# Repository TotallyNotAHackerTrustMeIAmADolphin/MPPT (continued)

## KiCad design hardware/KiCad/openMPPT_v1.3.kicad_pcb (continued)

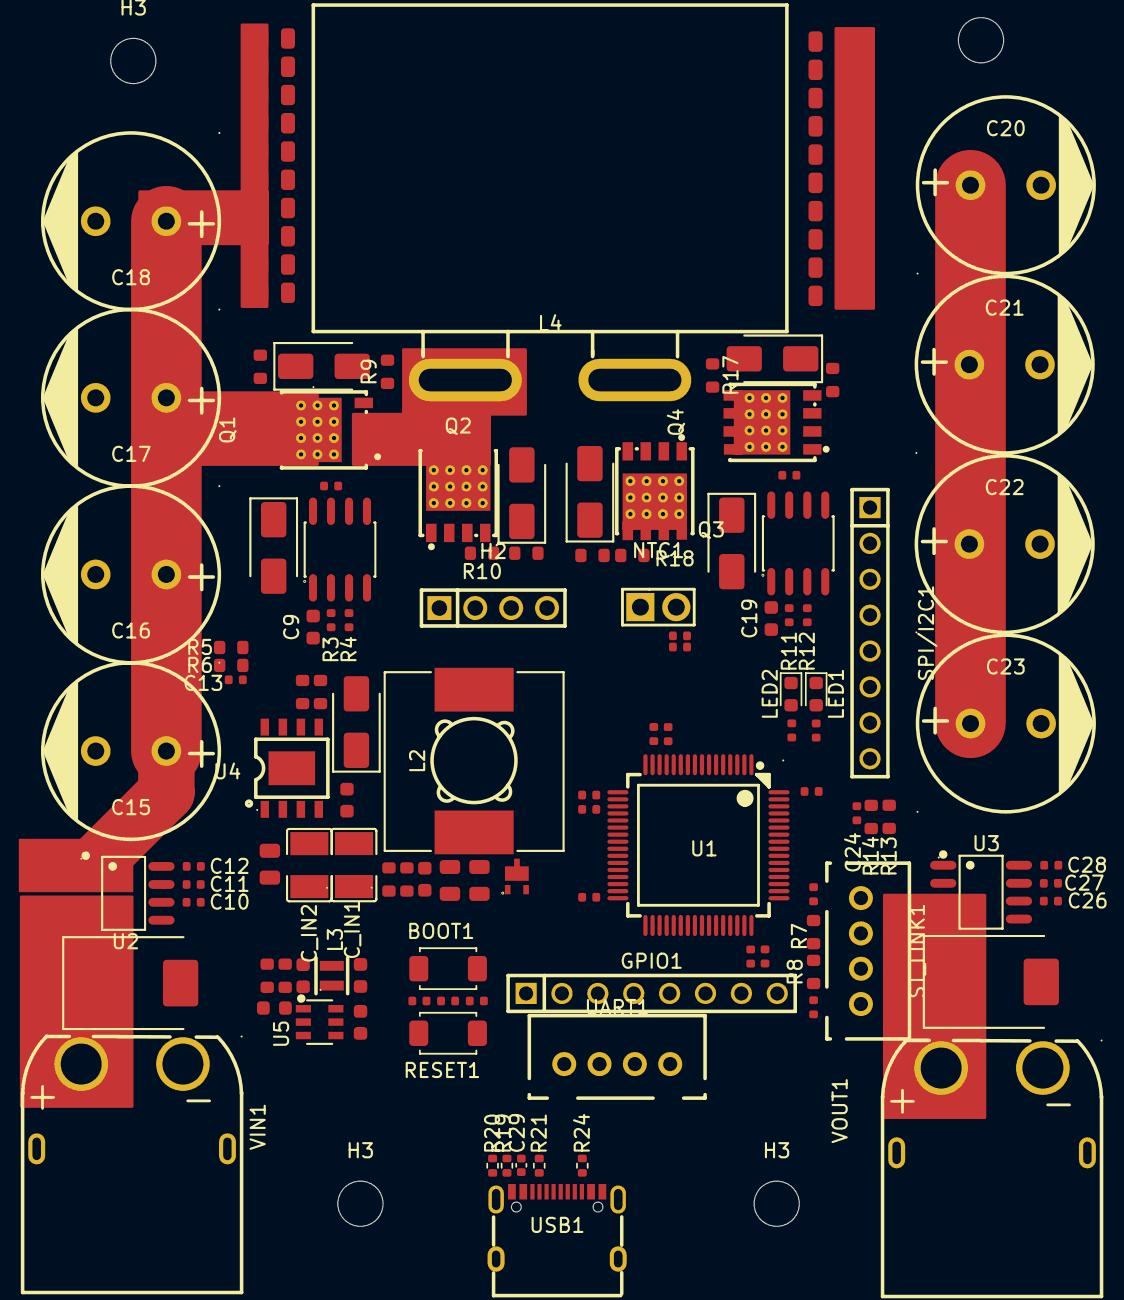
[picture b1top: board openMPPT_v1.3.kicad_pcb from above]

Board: 2 copper layers, 138 parts (0 on the bottom side), 68 nets.

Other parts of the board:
H3#2, H3#3: MountingHole; MountingHole_3.2mm_M3_DIN965

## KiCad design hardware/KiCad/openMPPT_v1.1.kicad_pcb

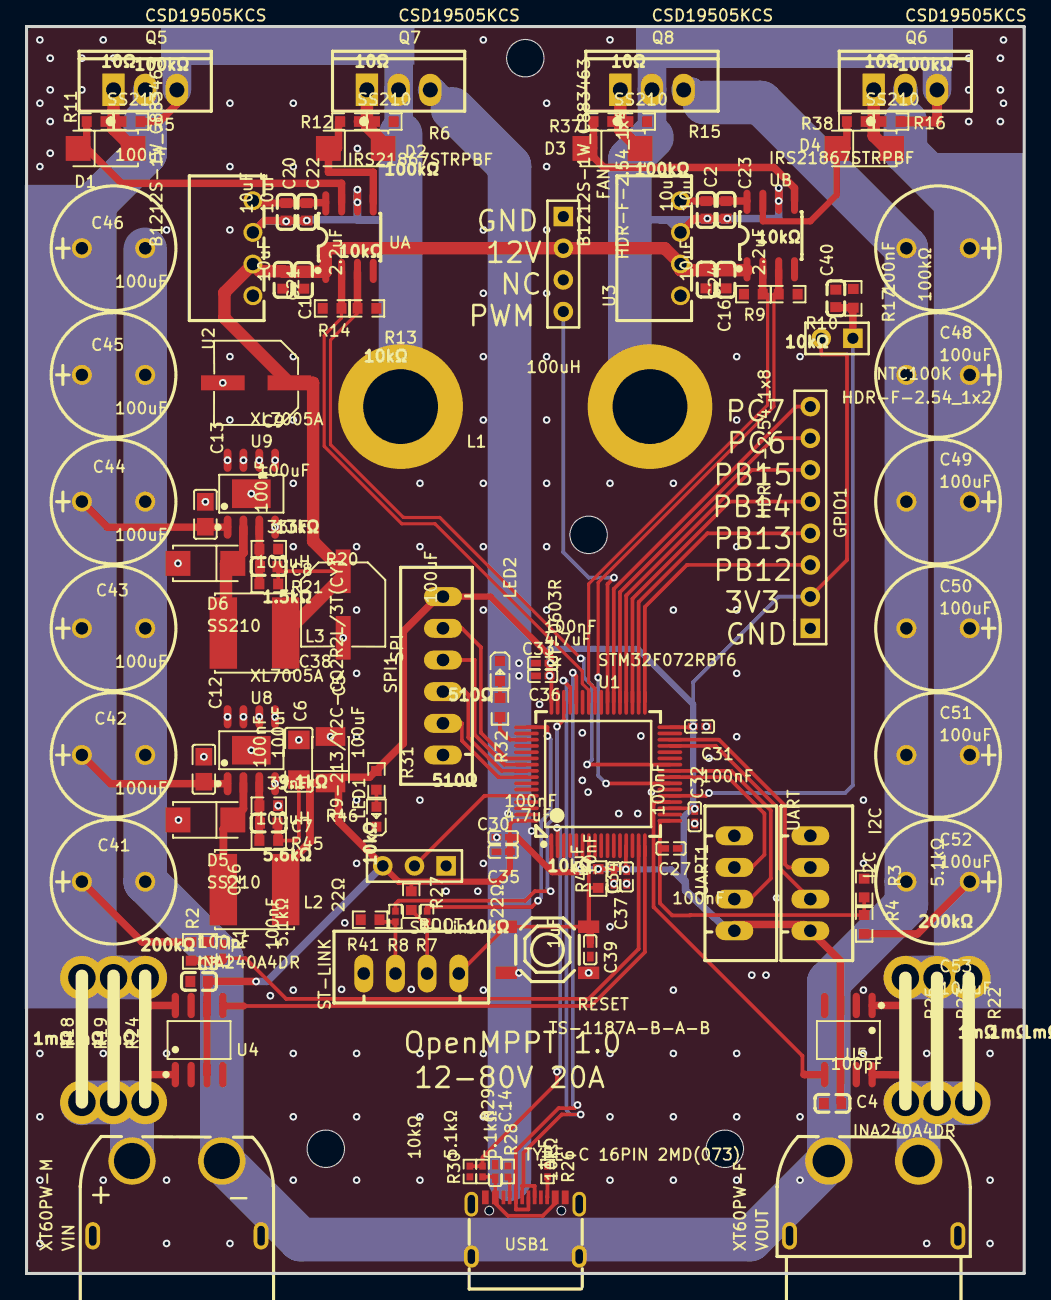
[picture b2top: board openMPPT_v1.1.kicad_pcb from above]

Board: 2 copper layers, 80.0 x 100.0 mm, 121 parts (0 on the bottom side), 62 nets.

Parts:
BOOT1: BOOT; HDR-F-2.54_1X3
C1, C2, C16, C20, C22, C23: 10uF; C0603
C3, C4: 100pF; C0603
C5: 100uF; C1206
C6: 100uF; CASE-B_3528
C7, C8: 33nF; C0603
C9, C38: 100uF; CAP-SMD_BD6.3-L6.6-W6.6-FD
C12, C13: 100nF; C0805
C14, C37, C39: 1uF; C0402
C21, C24: 2.2uF; C0603
C26, C27, C30, C31, C32, C33: 100nF; C0402
C34: 10nF; C0402
C35, C36: 4.7uF; C0402
C40: 100nF; C0603
C41, C42, C43, C44, C45, C46, C48, C49, C50, C51, C52, C53: 100uF; CAP-TH_BD10.0-P5.00-D1.0-FD
D1, D2, D3, D4, D5, D6: SS210; SMA_L4.3-W2.6-LS5.2-RD
FAN: HDR-F-2.54_1x4; HDR-F-2.54_1X4
GPIO1: HDR-F-2.54_1x8; HDR-F-2.54_1X8
Hole_gge64515: Hole_gge64515
Hole_gge4170615605543658: Hole_gge4170615605543658
Hole_gge4170615605543673: Hole_gge4170615605543673
Hole_gge4170615605579758: Hole_gge4170615605579758
I2C: I2C; JST-XH-04-PACKAGE-LONG-PAD
L1: 100uH; INDUCTOR1
L2, L3: 100uH; IND-SMD_L6.0-W6.0
LED1: 19-213/Y2C-CQ2R2L/3T(CY); LED0603-RD-YELLOW
LED2: KT-0603R; LED0603-RD
NTC100K: HDR-F-2.54_1x2; HDR-F-2.54_1X2
Q5, Q6, Q7, Q8: CSD19505KCS; TO-220-3_L10.0-W4.5-P2.54-L
R1, R3: 5.1kΩ; R0603
R2, R4: 200kΩ; R0603
R5, R6, R15, R16, R17: 100kΩ; R0603
R7, R8: 22Ω; R0402
R9, R10, R13, R14, R27, R41, R42: 10kΩ; R0603
R11, R12, R37, R38: 10Ω; R0603
R18, R19, R22, R23, R24, R25: 1mΩ; WIRE-SHUNT
R20: 1.5kΩ; R0603
R21: 13kΩ; R0603
R26, R28: 5.1kΩ; R0402
R29, R30: 10kΩ; R0402
R31, R32: 510Ω; R0603
R45: 9.1kΩ; R0603
R46: 5.6kΩ; R0603
RESET: TS-1187A-B-A-B; SW-SMD_4P-L5.1-W5.1-P3.70-LS6.5-TL-2
SPI1: SPI; JST-XH-06-PACKAGE-LONG-PAD
ST-LINK: ST-Link; JST-XH-04-PACKAGE-LONG-PAD
U1: STM32F072RBT6; LQFP-64_L10.0-W10.0-P0.50-LS12.0-BL
U2, U3: B1212S-1W_C883463; PWRM-TH_B2415S-1W
U4, U5: INA240A4DR; SOIC-8_L4.9-W3.9-P1.27-LS6.0-BL
U8, U9: XL7005A; SOIC-8_L4.9-W3.9-P1.27-LS6.0-BL-EP3.1-1
UA: IRS21867STRPBF; SOIC-8_L5.0-W4.0-P1.27-LS6.0-BL
UART1: UART; JST-XH-04-PACKAGE-LONG-PAD
UB: IRS21867STRPBF; SOIC-8_L5.0-W4.0-P1.27-LS6.0-BL
USB1: TYPE-C 16PIN 2MD(073); USB-C-SMD_TYPE-C-6PIN-2MD-073
VIN: XT60PW-M; CONN-TH_XT60PW-M
VOUT: XT60PW-F; CONN-TH_XT60PW-F

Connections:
3V3: BOOT1.3, C3.2, C4.2, C5.2, C6.1, C7.2, C30.2, C31.2, C32.2, C33.2, C34.2, C35.2, C36.2, C37.2, GPIO1.2, I2C.4, L2.2, NTC100K.2, R27.1, R31.1, R42.2, R45.2, SPI1.6, U1.1, U1.13, U1.19, U1.32, U1.48, U1.64, U4.3, U4.6, U5.3, U5.6, UART1.4
12V: C1.2, C8.2, C9.1, C16.2, C21.1, C24.1, C38.1, FAN.2, L3.2, R21.2, U2.2, U3.2, UA.1, UB.1
BOOT0: BOOT1.2, U1.60
C2_2: C2.2, C23.2, U3.4, UB.8
C8_1: C8.1, R20.2, R21.1, U9.3
CS: SPI1.5, U1.54
D1_1: D1.1, R11.1, UA.7
D2_1: D2.1, R12.1, UA.5
D3_1: D3.1, R37.1, UB.5
D4_1: D4.1, R38.1, UB.7
D6_1: D6.1, L3.1, U9.2
FAN: FAN.4, U1.39
GND: BOOT1.1, C1.1, C3.1, C4.1, C5.1, C6.2, C9.2, C12.1, C13.1, C14.1, C16.1, C21.2, C24.2, C26.1, C27.1, C30.1, C31.1, C32.1, C33.1, C34.1, C35.1, C36.1, C37.1, C38.2, C39.1, C40.1, C41.2, C42.2, C43.2, C44.2, C45.2, C46.2, C48.2, C49.2, C50.2, C51.2, C52.2, C53.2, D5.2, D6.2, FAN.1, GPIO1.1, I2C.1, LED1.1, LED2.1, Q7.3, Q8.3, R1.1, R3.1, R6.1, R9.1, R10.1, R13.1, R14.1, R15.1, R17.1, R20.1, R26.2, R28.2, R30.1, R41.1, R46.1, RESET.1, RESET.2, SPI1.1, ST-LINK.1, U1.12, U1.18, U1.31, U1.47, U1.63, U2.1, U3.1, U4.2, U4.7, U5.2, U5.7, U8.4, U8.5, U8.6, U8.7, U8.8, U8.9, U9.4, U9.5, U9.6, U9.7, U9.8, U9.9, UA.4, UART1.1, UB.4, USB1.1, USB1.12, USB1.13, USB1.14, VIN.1, VIN.3, VIN.4, VOUT.2, VOUT.3, VOUT.4
HO_A: D1.2, Q5.1, R5.1, R11.2
HO_B: D4.2, Q6.1, R16.1, R38.2
ISENSEIN: U1.16, U4.5
ISENSEOUT: U1.20, U5.5
LED: R32.1, U1.51
LO_A: D2.2, Q7.1, R6.2, R12.2
LO_B: D3.2, Q8.1, R15.2, R37.2
MISO: SPI1.3, U1.56
MOSI: SPI1.2, U1.57
NRST: C39.2, R42.1, RESET.3, RESET.4, ST-LINK.4, U1.7
NTC100K: C40.2, NTC100K.1, R17.2, U1.21
PB12: GPIO1.3, U1.33
PB13: GPIO1.4, U1.34
PB14: GPIO1.5, U1.35
PB15: GPIO1.6, U1.36
PC6: GPIO1.7, U1.37
PC7: GPIO1.8, U1.38
R26_1: R26.1, USB1.10
R27_2: R7.2, R27.2, ST-LINK.3
R28_1: R28.1, USB1.4
R29_2: C14.2, R29.2, USB1.2, USB1.11
R31_2: LED1.2, R31.2
R32_2: LED2.2, R32.2
R41_2: R8.1, R41.2, ST-LINK.2
RX: U1.25, UART1.3
SCK: SPI1.4, U1.55
SCL: I2C.3, U1.29
SDA: I2C.2, U1.30
SHUNT_IN+: C12.2, C13.2, C41.1, C42.1, C43.1, C44.1, C45.1, C46.1, Q5.2, R2.2, R18.2, R19.2, R24.2, U4.8, U8.1, U9.1
SHUNT_OUT-: C48.1, C49.1, C50.1, C51.1, C52.1, C53.1, Q6.2, R4.2, R22.1, R23.1, R25.1, U5.1
SWCLK: R7.1, U1.49
SWDIO: R8.2, U1.46
TIM1_CH1: R9.2, U1.41, UB.2
TIM1_CH1N: R10.2, U1.23, UB.3
TIM1_CH2: R14.2, U1.42, UA.2
TIM1_CH2N: R13.2, U1.26, UA.3
TX: U1.24, UART1.2
U2_4: C20.2, C22.2, U2.4, UA.8
U8_2: D5.1, L2.1, U8.2
U8_3: C7.1, R45.1, R46.2, U8.3
USB_DM: U1.44, USB1.5, USB1.7
USB_DP: U1.45, USB1.6, USB1.8
VBUS: R29.1, R30.2, U1.2
VIN: R18.1, R19.1, R24.1, U4.1, VIN.2
VOUT: R22.2, R23.2, R25.2, U5.8, VOUT.1
VSENSEIN: C26.2, R1.2, R2.1, U1.15
VSENSEOUT: C27.2, R3.2, R4.1, U1.17
VS_A: C20.1, C22.1, L1.1, Q5.3, Q7.2, R5.2, U2.3, UA.6
VS_B: C2.1, C23.1, L1.2, Q6.3, Q8.2, R16.2, U3.3, UB.6

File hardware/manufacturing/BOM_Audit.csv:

"Refs","Value","Footprint","Qty","DNP"
"?","A_A4","ProPrj_STM-easyedapro:","1",""
"?","A_A4","ProPrj_STM-easyedapro:","1",""
"?","A_A4","ProPrj_STM-easyedapro:","1",""
"BOOT1","BOOT","ProPrj_STM-easyedapro:HDR-F-2.54_1X3","1",""
"C1","10uF","ProPrj_STM-easyedapro:C0603","1",""
"C2","10uF","ProPrj_STM-easyedapro:C0603","1",""
"C3","100pF","ProPrj_STM-easyedapro:C0603","1",""
"C4","100pF","ProPrj_STM-easyedapro:C0603","1",""
"C5","100uF","ProPrj_STM-easyedapro:C1206","1",""
"C6","100uF","ProPrj_STM-easyedapro:CASE-B_3528","1",""
"C7","33nF","ProPrj_STM-easyedapro:C0603","1",""
"C8","33nF","ProPrj_STM-easyedapro:C0603","1",""
"C9","100uF","ProPrj_STM-easyedapro:CAP-SMD_BD6.3-L6.6-W6.6-FD","1",""
"C10","100nF","ProPrj_STM-easyedapro:C0603","1",""
"C11","100nF","ProPrj_STM-easyedapro:C0603","1",""
"C12","100nF","ProPrj_STM-easyedapro:C0402","1",""
"C13","100nF","ProPrj_STM-easyedapro:C0402","1",""
"C14","1uF","ProPrj_STM-easyedapro:C0402","1",""
"C16","10uF","ProPrj_STM-easyedapro:C0603","1",""
"C20","10uF","ProPrj_STM-easyedapro:C0603","1",""
"C21","2.2uF","ProPrj_STM-easyedapro:C0603","1",""
"C22","10uF","ProPrj_STM-easyedapro:C0603","1",""
"C23","10uF","ProPrj_STM-easyedapro:C0603","1",""
"C24","2.2uF","ProPrj_STM-easyedapro:C0603","1",""
"C26","100nF","ProPrj_STM-easyedapro:C0402","1",""
"C27","100nF","ProPrj_STM-easyedapro:C0402","1",""
"C30","100nF","ProPrj_STM-easyedapro:C0402","1",""
"C31","100nF","ProPrj_STM-easyedapro:C0402","1",""
"C32","100nF","ProPrj_STM-easyedapro:C0402","1",""
"C33","100nF","ProPrj_STM-easyedapro:C0402","1",""
"C34","10nF","ProPrj_STM-easyedapro:C0402","1",""
"C35","4.7uF","ProPrj_STM-easyedapro:C0402","1",""
"C36","4.7uF","ProPrj_STM-easyedapro:C0402","1",""
"C37","1uF","ProPrj_STM-easyedapro:C0402","1",""
"C38","100uF","ProPrj_STM-easyedapro:CAP-SMD_BD6.3-L6.6-W6.6-FD","1",""
"C39","1uF","ProPrj_STM-easyedapro:C0402","1",""
"C40","100nF","ProPrj_STM-easyedapro:C0603","1",""
"C41","100uF","ProPrj_STM-easyedapro:CAP-TH_BD10.0-P5.00-D1.0-FD","1",""
"C42","100uF","ProPrj_STM-easyedapro:CAP-TH_BD10.0-P5.00-D1.0-FD","1",""
"C43","100uF","ProPrj_STM-easyedapro:CAP-TH_BD10.0-P5.00-D1.0-FD","1",""
"C44","100uF","ProPrj_STM-easyedapro:CAP-TH_BD10.0-P5.00-D1.0-FD","1",""
"C45","100uF","ProPrj_STM-easyedapro:CAP-TH_BD10.0-P5.00-D1.0-FD","1",""
"C46","100uF","ProPrj_STM-easyedapro:CAP-TH_BD10.0-P5.00-D1.0-FD","1",""
"C48","100uF","ProPrj_STM-easyedapro:CAP-TH_BD10.0-P5.00-D1.0-FD","1",""
"C49","100uF","ProPrj_STM-easyedapro:CAP-TH_BD10.0-P5.00-D1.0-FD","1",""
"C50","100uF","ProPrj_STM-easyedapro:CAP-TH_BD10.0-P5.00-D1.0-FD","1",""
"C51","100uF","ProPrj_STM-easyedapro:CAP-TH_BD10.0-P5.00-D1.0-FD","1",""
"C52","100uF","ProPrj_STM-easyedapro:CAP-TH_BD10.0-P5.00-D1.0-FD","1",""
"C53","100uF","ProPrj_STM-easyedapro:CAP-TH_BD10.0-P5.00-D1.0-FD","1",""
"D1","SS210","ProPrj_STM-easyedapro:SMA_L4.3-W2.6-LS5.2-RD","1",""
"D2","SS210","ProPrj_STM-easyedapro:SMA_L4.3-W2.6-LS5.2-RD","1",""
"D3","SS210","ProPrj_STM-easyedapro:SMA_L4.3-W2.6-LS5.2-RD","1",""
"D4","SS210","ProPrj_STM-easyedapro:SMA_L4.3-W2.6-LS5.2-RD","1",""
"D5","SS210","ProPrj_STM-easyedapro:SMA_L4.3-W2.6-LS5.2-RD","1",""
"D6","SS210","ProPrj_STM-easyedapro:SMA_L4.3-W2.6-LS5.2-RD","1",""
"FAN?","HDR-F-2.54_1x4","ProPrj_STM-easyedapro:HDR-F-2.54_1X4","1",""
"GPIO1","HDR-F-2.54_1x8","ProPrj_STM-easyedapro:HDR-F-2.54_1X8","1",""
"I2C?","I2C","ProPrj_STM-easyedapro:JST-XH-04-PACKAGE-LONG-PAD","1",""
"L1","100uH","ProPrj_STM-easyedapro:IND-SMD_L6.0-W6.0","1",""
"L2","100uH","ProPrj_STM-easyedapro:IND-SMD_L6.0-W6.0","1",""
"L3","100uH","ProPrj_STM-easyedapro:IND-SMD_L6.0-W6.0","1",""
"LED1","19-213/Y2C-CQ2R2L/3T(CY)","ProPrj_STM-easyedapro:LED0603-RD-YELLOW","1",""
"LED2","KT-0603R","ProPrj_STM-easyedapro:LED0603-RD","1",""
"NTC100K?","HDR-F-2.54_1x2","ProPrj_STM-easyedapro:HDR-F-2.54_1X2","1",""
"Q5","CSD19505KCS","ProPrj_STM-easyedapro:TO-220-3_L10.0-W4.5-P2.54-L","1",""
"Q6","CSD19505KCS","ProPrj_STM-easyedapro:TO-220-3_L10.0-W4.5-P2.54-L","1",""
"Q7","CSD19505KCS","ProPrj_STM-easyedapro:TO-220-3_L10.0-W4.5-P2.54-L","1",""
"Q8","CSD19505KCS","ProPrj_STM-easyedapro:TO-220-3_L10.0-W4.5-P2.54-L","1",""
"R1","5.1Ω","ProPrj_STM-easyedapro:R0603","1",""
"R2","200kΩ","ProPrj_STM-easyedapro:R0603","1",""
"R3","5.1Ω","ProPrj_STM-easyedapro:R0603","1",""
"R4","200kΩ","ProPrj_STM-easyedapro:R0603","1",""
"R5","100kΩ","ProPrj_STM-easyedapro:R0603","1",""
"R6","100kΩ","ProPrj_STM-easyedapro:R0603","1",""
"R9","10kΩ","ProPrj_STM-easyedapro:R0402","1",""
"R10","10kΩ","ProPrj_STM-easyedapro:R0402","1",""
"R11","10Ω","ProPrj_STM-easyedapro:R0603","1",""
"R12","10Ω","ProPrj_STM-easyedapro:R0603","1",""
"R13","10kΩ","ProPrj_STM-easyedapro:R0402","1",""
"R14","10kΩ","ProPrj_STM-easyedapro:R0402","1",""
"R15","100kΩ","ProPrj_STM-easyedapro:R0603","1",""
"R16","100kΩ","ProPrj_STM-easyedapro:R0603","1",""
"R17","100kΩ","ProPrj_STM-easyedapro:R0603","1",""
"R18","1mΩ","ProPrj_STM-easyedapro:WIRE-SHUNT","1",""
"R19","1mΩ","ProPrj_STM-easyedapro:WIRE-SHUNT","1",""
"R20","1.5kΩ","ProPrj_STM-easyedapro:R0603","1",""
"R21","13kΩ","ProPrj_STM-easyedapro:R0603","1",""
"R22","1mΩ","ProPrj_STM-easyedapro:WIRE-SHUNT","1",""
"R23","1mΩ","ProPrj_STM-easyedapro:WIRE-SHUNT","1",""
"R24","1mΩ","ProPrj_STM-easyedapro:WIRE-SHUNT","1",""
"R25","1mΩ","ProPrj_STM-easyedapro:WIRE-SHUNT","1",""
"R26","5.1kΩ","ProPrj_STM-easyedapro:R0402","1",""
"R27","10kΩ","ProPrj_STM-easyedapro:R0402","1",""
"R28","5.1kΩ","ProPrj_STM-easyedapro:R0402","1",""
"R29","10kΩ","ProPrj_STM-easyedapro:R0402","1",""
"R30","10kΩ","ProPrj_STM-easyedapro:R0402","1",""
"R31","510Ω","ProPrj_STM-easyedapro:R0603","1",""
"R32","510Ω","ProPrj_STM-easyedapro:R0603","1",""
"R37","10Ω","ProPrj_STM-easyedapro:R0603","1",""
"R38","10Ω","ProPrj_STM-easyedapro:R0603","1",""
"R41","10kΩ","ProPrj_STM-easyedapro:R0402","1",""
"R42","10kΩ","ProPrj_STM-easyedapro:R0402","1",""
"R45","9.1kΩ","ProPrj_STM-easyedapro:R0603","1",""
"R46","5.6kΩ","ProPrj_STM-easyedapro:R0603","1",""
"RESET?","TS-1187A-B-A-B","ProPrj_STM-easyedapro:SW-SMD_4P-L5.1-W5.1-P3.70-LS6.5-TL-2","1",""
"SPI1","SPI","ProPrj_STM-easyedapro:JST-XH-06-PACKAGE-LONG-PAD","1",""
"ST-LINK1","ST-Link","ProPrj_STM-easyedapro:JST-XH-04-PACKAGE-LONG-PAD","1",""
"U1","STM32F072RBT6","ProPrj_STM-easyedapro:LQFP-64_L10.0-W10.0-P0.50-LS12.0-BL","1",""
"U2","B1212S-1W_C883463","ProPrj_STM-easyedapro:PWRM-TH_B2415S-1W","1",""
"U3","B1212S-1W_C883463","ProPrj_STM-easyedapro:PWRM-TH_B2415S-1W","1",""
"U4","INA240A4DR","ProPrj_STM-easyedapro:SOIC-8_L4.9-W3.9-P1.27-LS6.0-BL","1",""
"U5","INA240A4DR","ProPrj_STM-easyedapro:SOIC-8_L4.9-W3.9-P1.27-LS6.0-BL","1",""
"U8","XL7005A","ProPrj_STM-easyedapro:SOIC-8_L4.9-W3.9-P1.27-LS6.0-BL-EP3.1-1","1",""
"U9","XL7005A","ProPrj_STM-easyedapro:SOIC-8_L4.9-W3.9-P1.27-LS6.0-BL-EP3.1-1","1",""
"U?","Sort_Symbol","ProPrj_STM-easyedapro:","1",""
"U?","Sort_Symbol","ProPrj_STM-easyedapro:","1",""
"U?","Sort_Symbol","ProPrj_STM-easyedapro:","1",""
"U?","Sort_Symbol","ProPrj_STM-easyedapro:","1",""
"UA?","IRS21867STRPBF","ProPrj_STM-easyedapro:SOIC-8_L5.0-W4.0-P1.27-LS6.0-BL","1",""
"UART1","UART","ProPrj_STM-easyedapro:JST-XH-04-PACKAGE-LONG-PAD","1",""
"UB?","IRS21867STRPBF","ProPrj_STM-easyedapro:SOIC-8_L5.0-W4.0-P1.27-LS6.0-BL","1",""
"USB1","TYPE-C 16PIN 2MD(073)","ProPrj_STM-easyedapro:USB-C-SMD_TYPE-C-6PIN-2MD-073","1",""
"VIN1","XT60PW-F","ProPrj_STM-easyedapro:CONN-TH_XT60PW-M","1",""
"VOUT1","XT60PW-M","ProPrj_STM-easyedapro:CONN-TH_XT60PW-M","1",""

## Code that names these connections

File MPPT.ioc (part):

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Mcu.Name=STM32F072R(8-B)Tx
Mcu.Package=LQFP64
Mcu.UserName=STM32F072RBTx
PA1.GPIOParameters=GPIO_Label
PA1.GPIO_Label=VsenseIn
PA1.Mode=IN1
PA1.Signal=ADC_IN1
PA11.Mode=Device
PA11.Signal=USB_DM
PA12.Mode=Device
PA12.Signal=USB_DP
PA13.Mode=Serial_Wire
PA13.Signal=SYS_SWDIO
PA14.Mode=Serial_Wire
PA14.Signal=SYS_SWCLK
PA2.GPIOParameters=GPIO_Label
PA2.GPIO_Label=IsenseIn
PA2.Mode=IN2
PA2.Signal=ADC_IN2
PA3.GPIOParameters=GPIO_Label
PA3.GPIO_Label=VsenseOut
PA3.Mode=IN3
PA3.Signal=ADC_IN3
PA4.GPIOParameters=GPIO_Label
PA4.GPIO_Label=IsenseOut
PA4.Mode=IN4
PA4.Signal=ADC_IN4
PA5.GPIOParameters=GPIO_Label
PA5.GPIO_Label=NTC100K
PA5.Mode=IN5
PA5.Signal=ADC_IN5
PA7.GPIOParameters=GPIO_Label
PA7.GPIO_Label=boostLOWside
PA7.Mode=PWM Generation1 CH1 CH1N
PA7.Signal=TIM1_CH1N
PA8.GPIOParameters=GPIO_Label
PA8.GPIO_Label=boostHIGHside
PA8.Signal=S_TIM1_CH1
PA9.GPIOParameters=GPIO_Label
PA9.GPIO_Label=buckHIGHside
PA9.Signal=S_TIM1_CH2
PB0.GPIOParameters=GPIO_Label
PB0.GPIO_Label=buckLOWside
PB0.Mode=PWM Generation2 CH2 CH2N
PB0.Signal=TIM1_CH2N
PB10.Mode=I2C
PB10.Signal=I2C2_SCL
PB11.Mode=I2C
PB11.Signal=I2C2_SDA
PB3.Mode=Full_Duplex_Master
PB3.Signal=SPI1_SCK
PB4.Mode=Full_Duplex_Master
PB4.Signal=SPI1_MISO
PB5.Mode=Full_Duplex_Master
PB5.Signal=SPI1_MOSI
PC10.GPIOParameters=GPIO_Label
PC10.GPIO_Label=LED
PC10.Signal=GPIO_Output
PC13.GPIOParameters=GPIO_Label
PC13.GPIO_Label=usbDetect
PC13.Signal=GPIO_Input
PC4.Mode=Asynchronous
PC4.Signal=USART3_TX
PC5.Mode=Asynchronous
PC5.Signal=USART3_RX
PC8.GPIOParameters=GPIO_Label
PC8.GPIO_Label=fanControllPin
PC8.Signal=S_TIM3_CH3
PD2.GPIOParameters=GPIO_Label
PD2.GPIO_Label=chipSelect
PD2.Signal=GPIO_Output
RCC.SYSCLKFreq_VALUE=48000000
RCC.SYSCLKSource=RCC_SYSCLKSOURCE_HSI48
board=custom

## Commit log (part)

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2024-06-01 minor changes
2024-07-25 Start from scratch
2024-07-25 removed pio folder
2024-07-29 better calibration capabilites and sensor readout
2024-08-07 Made MPPT algorithm faster and more reliable
2024-08-19 mayor improvements of MPPT algorithm
2026-05-17 Revert "complete refactoring. (untested)"
    This reverts commit 31651d1582f6ce1805b2514ffdd31b842b5b62cc.
2026-05-17 Convert entire codebase to Semantic Fixed-Point math
    - Replaced all floating-point math with 32-bit and 64-bit integer arithmetic.
    - Renamed variables to include semantic units (e.g., voltageIn_mV, currentIn_mA, powerIn_uW).
    - Refactored readSensors and calibrateSensors to use efficient integer scaling.
    - Refactored PID and MPPT controllers to use dithered timer ticks directly.
    - Updated telemetry printf strings to use integer format specifiers.
    - Updated GEMINI.md to reflect new architecture and conventions.
2026-05-17 Document USB DFU Auto-Reset feature
2026-05-17 Revert "Finalize DFU auto-reset and memory preservation logic"
    This reverts commit 13746b93ea540ae97f24eaf1bad5cc2ae2c4f8fc.
2026-05-17 Revert all DFU-related changes and clean up documentation
    - Removed 1200 baud touch logic from usbd_cdc_if.c.
    - Removed DFU jump logic and .noinit variable from main.c.
    - Removed .noinit section from linker script.
    - Reverted platformio.ini to use stlink upload protocol.
    - Cleaned up GEMINI.md and README.md to remove DFU auto-reset instructions.
2026-05-17 Hardware verification complete: MPPT sweep and Boost mode confirmed
    - Restored sweep interval to 300s after successful 30s testing.
    - Fixed efficiency telemetry scaling and printf formats.
    - Verified stable fixed-point operation under 28W load.
    - Confirmed Buck-to-Boost transition is functional and precise.
2026-05-17 Fixed compilation errors in Interactive Calibration feature
2026-05-17 Rename web/ to docs/ for GitHub Pages compatibility
2026-05-17 Optimize telemetry frequency and add raw calibration feedback
2026-05-18 added 3D file
2026-05-18 added kicad files
2026-05-18 docs: add hardware/ directory to GEMINI.md
2026-05-18 refactor: modularize codebase and implement unified state machine
    - Decomposed main.c into specialized modules (Sensors, Power, MPPT, Controller, Comms, Settings).
    - Implemented a unified system state machine with explicit transitions.
    - Added real-time system state display to the Web UI dashboard.
    - Standardized on Embedded C patterns and encapsulated internal states.
    - Switched to HAL_GetTick based timing for improved stability.
2026-05-18 fix: resolve USB lockup, implement safe EEPROM defaults, and enhance UI
    - Added timeout to USB TX loop in _write() to prevent boot lockup without host.
    - Implemented EEPROM signature check to ensure safe defaults on first flash.
    - Forced PWM shutdown during EEPROM saves to prevent controller/hardware crashes.
    - Added CMD:GET_LIMITS to synchronize dashboard with firmware state on connect.
    - Updated Dashboard UI to format telemetry in V/A/W and auto-fetch device limits.
    - Removed obsolete operational inputs for hardcoded safety limits.
2026-05-18 feat: display duty cycle in percent and finalize dashboard unit formatting
    - Implemented POWER_PWM_GetDutyCycle_x100 to calculate percentage with 0.01% precision.
    - Updated telemetry protocol to include duty_x100 instead of raw ticks.
    - Overhauled dashboard UI to display all telemetry values in readable units (V, A, W, %, °C).
    - Synchronized HTML element IDs with updated telemetry keys for duty cycle percentage.
2026-05-18 fix: eliminate USB connection requirement and prevent headless crashes
    - Added NULL pointer check in CDC_Transmit_FS to prevent HardFault when USB is disconnected.
    - Reduced iteration timeout in _write loop from 1,000,000 to 10,000 to ensure high-rate regulation continues smoothly even if USB host buffers are full.
    - Verified that the board now boots and regulates autonomously without a connected serial interface.
2026-05-18 fix: implement robust limit sync with auto-retry on connect
    The dashboard now sends CMD:GET_LIMITS every 2 seconds until it receives a valid response. This eliminates the race condition where the board might still be booting or re-enumerating USB when the fir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
2026-05-18 docs: overhaul README and GEMINI instructions to reflect new system architecture
    - Documented Velocity PI regulation and elimination of voltage ripple.
    - Added Hardware Safety Architecture details (OV, UV, OC limits).
    - Documented autonomous/headless boot and standalone operation fixes.
    - Updated MPPT section with optimized tracking and stabilization details.
    - Updated Web Dashboard and Telemetry documentation for standard units (V, A, W).
    - Added EEPROM safety and signature check conventions.
2026-05-18 fix: remove live limit syncing from telemetry to prevent input overwriting
    The 10Hz telemetry stream was fighting with the user by overwriting input fields before they could click 'Update'. Limits are now only populated once upon connection (via robust GET_LIMITS retry) or 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
2026-05-18 feat: implement autonomous brownout recovery logic
    - Updated STATE_FAULT handling to automatically transition back to STATE_IDLE when an INPUT_UNDERVOLTAGE fault is resolved (Vin > 14V).
    - This allows the system to resume charging autonomously without manual dashboard interaction after a temporary source collapse.
    - Verified seamless recovery and restart of the MPPT sweep during testing.
2026-05-18 chore: remove redundant limit fields and unused variable from telemetry
    - Removed Vmax_limit, Vmin_limit, and Imax_limit from the periodic telemetry JSON output.
    - Removed the unused 'limits' variable in COMMS_SendTelemetry to fix compilation error.
    - Streamlined serial bandwidth by focusing telemetry on real-time measurements.
2026-05-19 feat(docs): split calibration wizard into independent Voltage and Current flows
    Moved calibration launch buttons to a dedicated section below limits. Split the wizard into two independent paths to accommodate hardware power constraints. Added safety warnings and manual pass-thro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
2026-05-19 fix(power): correct pass-through duty cycle for calibration
    Modified calibration override to use 100% duty cycle (timer period) instead of max boost duty cycle. This prevents the input stage from switching and shorting the inductor during current calibration.
2026-05-19 refactor(sensors): consolidate EMA filtering to RAW ADC level
    Removed redundant mV-level filtering and replaced it with a single-stage high-precision EMA filter at the RAW ADC stage. All derived measurements (telemetry, dashboard raw values, and control loop) n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
2026-05-19 fix(sensors): dual-stage EMA filtering for speed and stability
    Implemented a dual-stage EMA filter: a FAST filter (alpha 0.5) for the MPPT control loop to eliminate phase lag-induced oscillation, and a SLOW filter (alpha 0.0625) for the dashboard calibration UI.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
2026-05-19 feat(mppt): implement high-performance Adaptive VSS P&O
    Upgraded the MPPT algorithm to Variable Step Size (VSS) using the |dP/dV| slope calculation. Reduced the MPPT interval to 20ms. This achieves significantly faster tracking during transients while eli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
2026-05-19 tune(mppt): dampen VSS for stable sources and add step telemetry
    Reduced VSS_N_FACTOR to 1 and VSS_MAX_STEP to 8 to prevent over-corrections on low-impedance power supplies. Added 'mppt_step' to serial telemetry for real-time algorithm monitoring.
2026-05-19 tune(mppt): loop iteration 3 - optimize for faster tracking
    Increased N_FACTOR to 3 and MAX_STEP to 20. Reduced interval to 20ms. This should provide much faster response to changing conditions while maintaining micro-step stability at the peak.
2026-05-19 tune(mppt): loop iteration 5 - ultra-stability
    Limited MAX_STEP to 10 and increased interval to 30ms. Lowered POWER_THRESHOLD_UW to 5mW. This configuration prioritizes rock-solid stability and precision over raw tracking speed.
2026-05-19 feat(mppt): implement high-stability 100ms Adaptive P&O
    Optimized the MPPT algorithm for high-voltage stability. Features 100ms settling time, Alpha 0.25 EMA filtering, and high-gain search scaling. Successfully verified stable tracking at 30W+ peak on 60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
2026-05-19 Add hardware tuning guide for the lab test phase.
2026-05-19 Set up native unit testing environment and add MPPT algorithm tests.
    - Added 'native' environment to platformio.ini for off-target testing.
    - Implemented unit tests for P&O algorithm (power increase, power decrease, brownout protection) in test/test_mppt/test_mppt.c.
    - Verified algorithm logic independently of hardware.
2026-05-19 feat: apply optimal 'Advanced Hill Climb' parameters
2026-05-19 chore: clean technical debt (fix deprecations and syntax warnings)
2026-05-20 Revert "feat: implement robust USB DFU trigger and jump mechanism"
    This reverts commit e967b7dd93cc7356b9f8e956725afbb2860c299a.
2026-05-20 feat: restore hardware safety hardening to main branch
2026-05-20 feat: implement unified override control and bidirectional e-bike mode
2026-05-21 feat: reflect operational logic changes in dashboard UI
    - Updated labels to flow-centric names (e.g., Output Voltage Limit, Input Soft-Floor).
    - Added a new control for the Reverse Current Limit (iOutMin).
    - Synchronized with new telemetry states (ACTIVE_CV, ACTIVE_BROWNOUT, etc.).
    - Color-coded descriptive active states in the dashboard state badge.
    - Synchronized DeviceLimits_t parsing with the updated firmware field names.
2026-05-21 fix: implement 'Hard-Zero' safety mechanism in power.c
    - Added hardware-level shutdown (MOE disable) when duty cycle is <2%.
    - Prevents synchronous Low-Side MOSFETs from shorting the battery to ground at 0% duty.
    - Ensures all regulation limits (including Reverse CV) have a safe 'High-Impedance' state to pull back to.
2026-05-29 docs: update architecture and tuning guide for unified control
    - Documented Unified Min-Selector architecture
    - Updated telemetry state definitions
    - Documented tuned PI gains and hysteresis parameters
2026-05-29 build: sync 16-tick dead-time optimization to CubeMX .ioc file
2026-05-29 fix: apply 16-tick dead-time optimization in TIM1 initialization
2026-05-29 docs: add diagnostic tool suite documentation and scripts
    - Add scripts/mppt_tool.py for advanced telemetry and control.
    - Add scripts/debug_mppt.py for simple CSV logging.
    - Update GEMINI.md with usage instructions for the diagnostic suite.
2026-05-29 docs: restore mathematical comments in mppt.c
2026-05-29 docs: add LED blink code reference to GEMINI.md
2026-05-29 refactor: remove No-Load Pressure logic, rely on fault recovery
2026-05-29 docs: add performance analysis and optimization roadmap
2026-05-29 fix: implement high-speed backflow protection and mandatory 13V brownout
2026-05-29 chore: increment dashboard and system versions, add versioning convention
2026-05-30 feat(hardware): initialize v1.3 roadmap, standards, and phase 1 power stage optimization
2026-05-30 docs(hardware): calculate optimal L/C values for 100kHz v1.3 power stage
2026-05-30 chore(hardware): backup custom kicad skill environment
2026-05-30 added the new 10v regulator
2026-05-30 finished 10V regulator
